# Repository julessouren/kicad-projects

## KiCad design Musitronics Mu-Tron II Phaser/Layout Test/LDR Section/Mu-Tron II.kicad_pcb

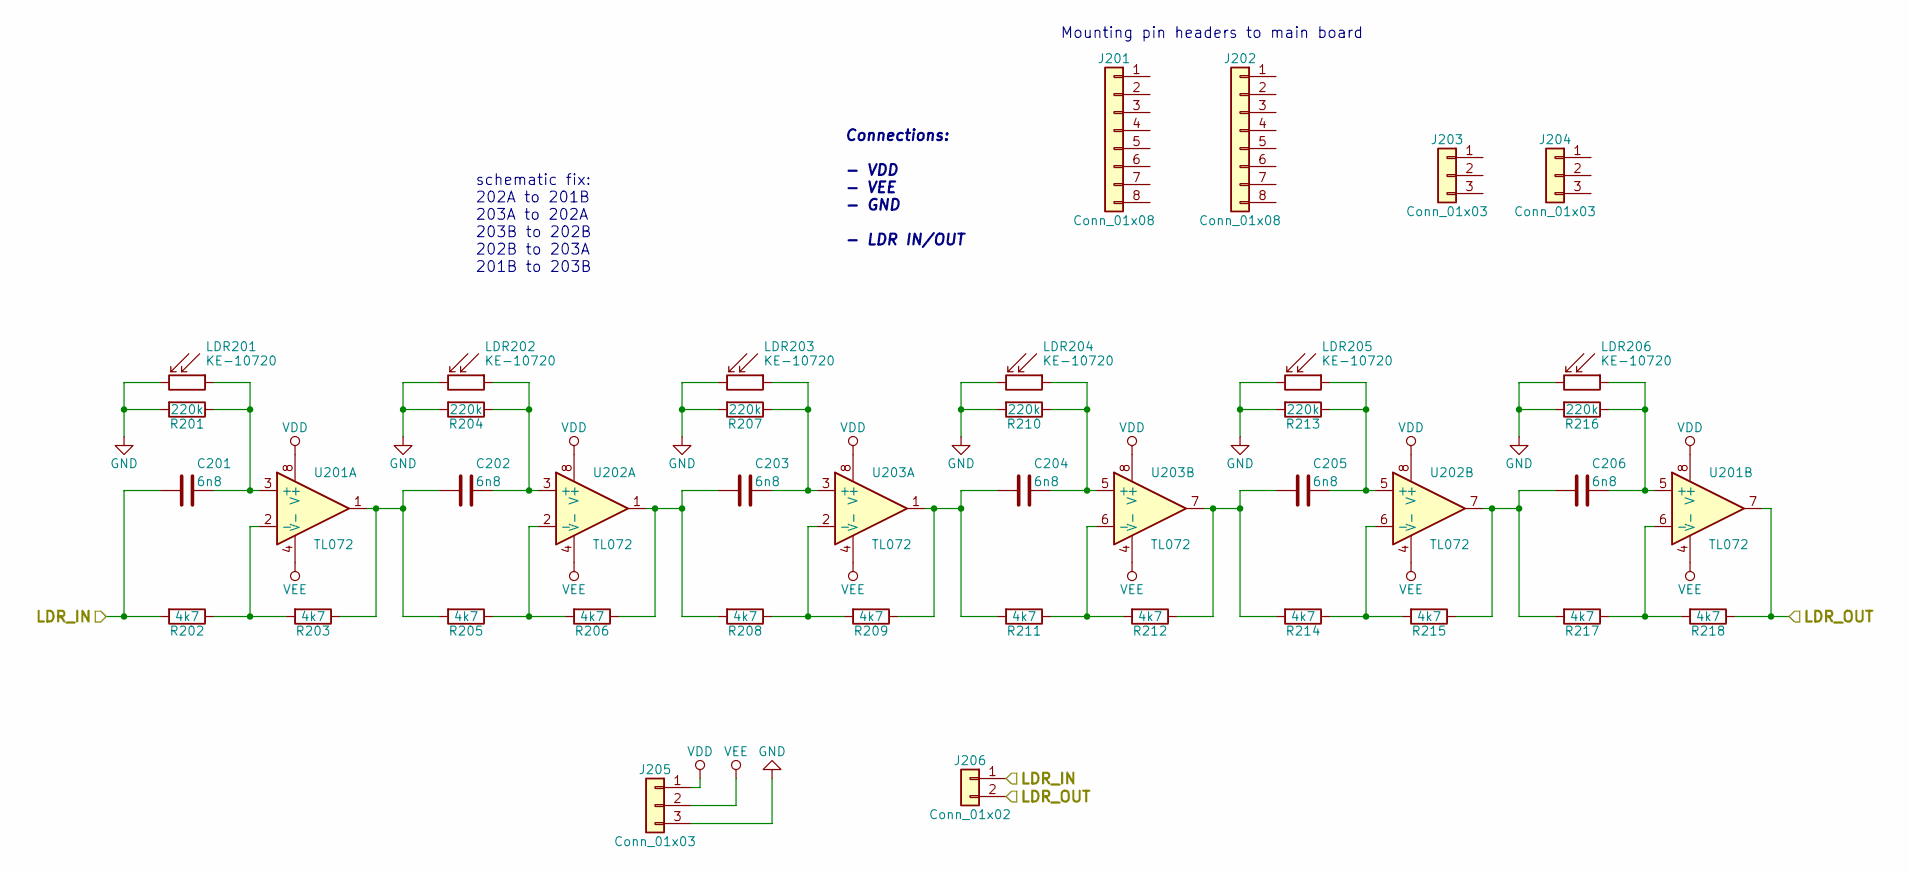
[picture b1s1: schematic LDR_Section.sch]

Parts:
C201, C202, C203, C204, C205, C206: 6n8; C_0603_1608M
J201, J202: Conn_01x08; PinHeader_1x08_P2.54mm_Vertical_Bottom
J203, J204, J205: Conn_01x03; PinHeader_1x03_P1.27mm_Vertical
J206: Conn_01x02; PinHeader_1x02_P1.27mm_Vertical
LDR201, LDR202, LDR203, LDR204, LDR205, LDR206: KE-10720; R_LDR_5.1x4.3mm_P3.4mm_Vertical
R201, R204, R207, R210, R213, R216: 220k; R_0603_1608M
R202, R203, R205, R206, R208, R209, R211, R212, R214, R215, R217, R218: 4k7; R_0603_1608M
U201, U202, U203: TL072; SOIC-8_3.9x4.9mm_P1.27mm

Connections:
/LDR_Section/LDR_IN: C201.2, J201.8, J206.1, R202.2
/LDR_Section/LDR_OUT: J202.8, J206.2, R218.1, U201.7
GND: J205.3, LDR201.2, LDR202.2, LDR203.2, LDR204.2, LDR205.2, LDR206.2, R201.2, R204.2, R207.2, R210.2, R213.2, R216.2; also elsewhere on the board
unnamed: C201.1, LDR201.1, R201.1, U201.3 (+)
unnamed: C202.1, LDR202.1, R204.1, U202.3 (+)
unnamed: C202.2, R203.1, R205.2, U201.1
unnamed: C203.1, LDR203.1, R207.1, U203.3 (+)
unnamed: C203.2, R206.1, R208.2, U202.1
unnamed: C204.1, LDR204.1, R210.1, U203.5 (+)
unnamed: C204.2, R209.1, R211.2, U203.1
unnamed: C205.1, LDR205.1, R213.1, U202.5 (+)
unnamed: C205.2, R212.1, R214.2, U203.7
unnamed: C206.1, LDR206.1, R216.1, U201.5 (+)
unnamed: C206.2, R215.1, R217.2, U202.7
unnamed: R202.1, R203.2, U201.2 (-)
unnamed: R205.1, R206.2, U202.2 (-)
unnamed: R208.1, R209.2, U203.2 (-)
unnamed: R211.1, R212.2, U203.6 (-)
unnamed: R214.1, R215.2, U202.6 (-)
unnamed: R217.1, R218.2, U201.6 (-)
VDD: J205.1, U201.8 (V+), U202.8 (V+), U203.8 (V+); also elsewhere on the board
VEE: J205.2, U201.4 (V-), U202.4 (V-), U203.4 (V-); also elsewhere on the board

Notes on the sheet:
Connections: - VDD - VEE - GND - LDR IN/OUT
Mounting pin headers to main board
schematic fix: 202A to 201B 203A to 202A 203B to 202B 202B to 203A 201B to 203B

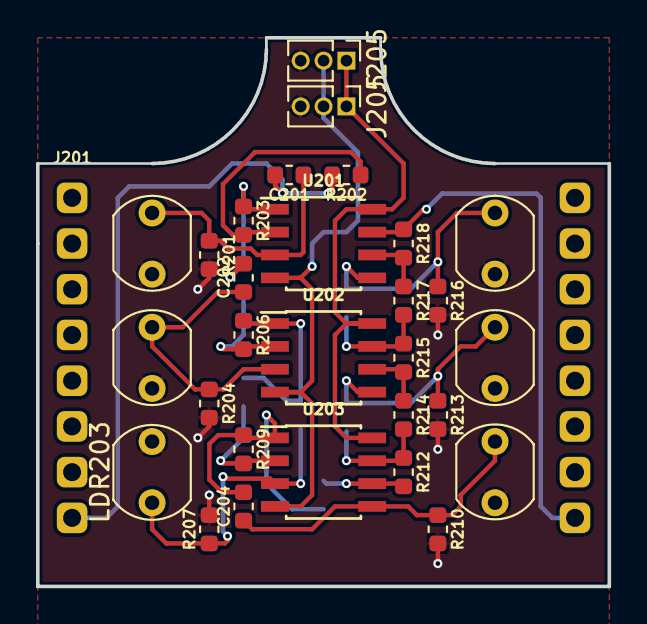
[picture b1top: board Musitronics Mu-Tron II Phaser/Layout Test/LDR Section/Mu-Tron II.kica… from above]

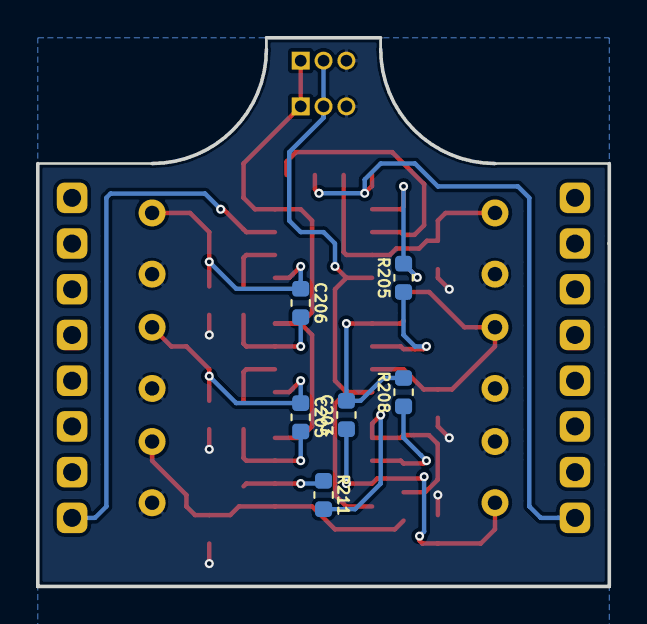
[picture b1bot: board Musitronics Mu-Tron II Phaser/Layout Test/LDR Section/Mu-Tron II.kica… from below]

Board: 2 copper layers, 31.8 x 30.5 mm, 37 parts (6 on the bottom side), 22 nets.

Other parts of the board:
J205#2: Conn_01x03; PinHeader_1x03_P1.27mm_Vertical

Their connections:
GND: J205#2.3; also elsewhere on the board
VDD: J205#2.1; also elsewhere on the board
VEE: J205#2.2; also elsewhere on the board

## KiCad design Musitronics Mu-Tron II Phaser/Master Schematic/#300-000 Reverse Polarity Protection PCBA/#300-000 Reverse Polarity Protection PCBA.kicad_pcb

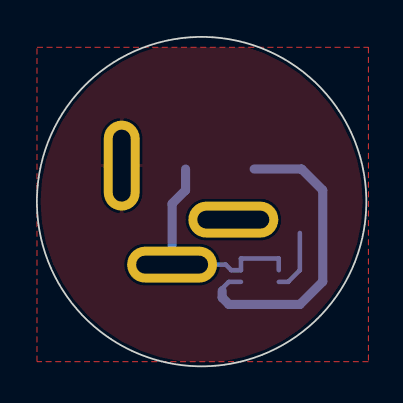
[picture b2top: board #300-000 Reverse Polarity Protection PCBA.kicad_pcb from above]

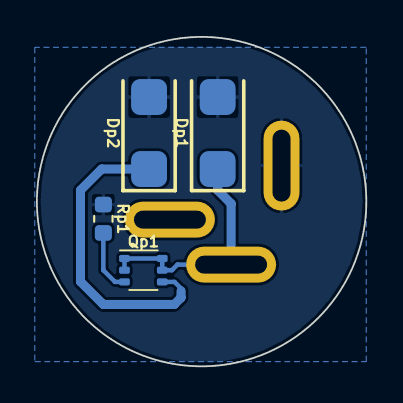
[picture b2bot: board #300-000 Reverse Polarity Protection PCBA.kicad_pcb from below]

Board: 2 copper layers, 18.3 x 18.3 mm, 5 parts (4 on the bottom side), 4 nets.

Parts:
Dp1, Dp2: 1SMA5924BT3G; ON_Semi_1SMA5924BT3G
Ja3: NEB_J_21_C; Lumberg_NEB_J_21_C
Qp1: MCH6341-TL-W; ON_Semi_MCH6341-TL-W
Rp1: 0R; R_0603_1608M

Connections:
GND: Dp1.1, Dp2.1, Ja3.1, Rp1.1
unnamed: Dp1.2, Ja3.2, Qp1.1, Qp1.2, Qp1.5, Qp1.6
unnamed: Qp1.3, Rp1.2
VCC: Dp2.2, Qp1.4

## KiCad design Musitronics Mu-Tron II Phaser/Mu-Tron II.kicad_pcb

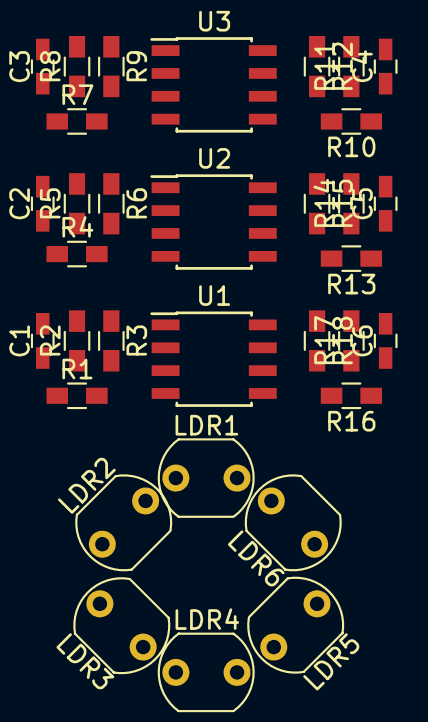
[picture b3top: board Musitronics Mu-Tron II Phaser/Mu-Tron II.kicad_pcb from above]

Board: 2 copper layers, 33 parts (0 on the bottom side), 20 nets, no tracks yet.

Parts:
C1, C2, C3, C4, C5, C6: 6n8; C_0603_HandSoldering
LDR1, LDR2, LDR3, LDR4, LDR5, LDR6: R_PHOTO; Resistor_LDR_5.1x4.3_RM3.4
R1, R4, R7, R10, R13, R16: 220k; R_0603_HandSoldering
R2, R3, R5, R6, R8, R9, R11, R12, R14, R15, R17, R18: 4k7; R_0603_HandSoldering
U1, U2, U3: NJM4558; SOIC-8_3.9x4.9mm_Pitch1.27mm

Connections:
GND: LDR1.2, LDR2.2, LDR3.2, LDR4.2, LDR5.2, LDR6.2, R1.2, R4.2, R7.2, R10.2, R13.2, R16.2, U1.4, U2.4, U3.4
unnamed: C1.1, LDR1.1, R1.1, U1.3
unnamed: C1.2, R2.2
unnamed: C2.1, LDR2.1, R4.1, U2.3
unnamed: C2.2, R3.1, R5.2, U1.1
unnamed: C3.1, LDR3.1, R7.1, U3.3
unnamed: C3.2, R6.1, R8.2, U2.1
unnamed: C4.1, LDR4.1, R10.1, U3.5
unnamed: C4.2, R9.1, R11.2, U3.1
unnamed: C5.1, LDR5.1, R13.1, U2.5
unnamed: C5.2, R12.1, R14.2, U3.7
unnamed: C6.1, LDR6.1, R16.1, U1.5
unnamed: C6.2, R15.1, R17.2, U2.7
unnamed: R2.1, R3.2, U1.2
unnamed: R5.1, R6.2, U2.2
unnamed: R8.1, R9.2, U3.2
unnamed: R11.1, R12.2, U3.6
unnamed: R14.1, R15.2, U2.6
unnamed: R17.1, R18.2, U1.6
unnamed: R18.1, U1.7

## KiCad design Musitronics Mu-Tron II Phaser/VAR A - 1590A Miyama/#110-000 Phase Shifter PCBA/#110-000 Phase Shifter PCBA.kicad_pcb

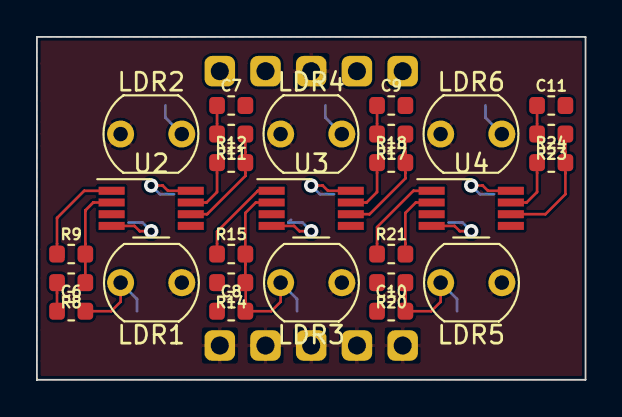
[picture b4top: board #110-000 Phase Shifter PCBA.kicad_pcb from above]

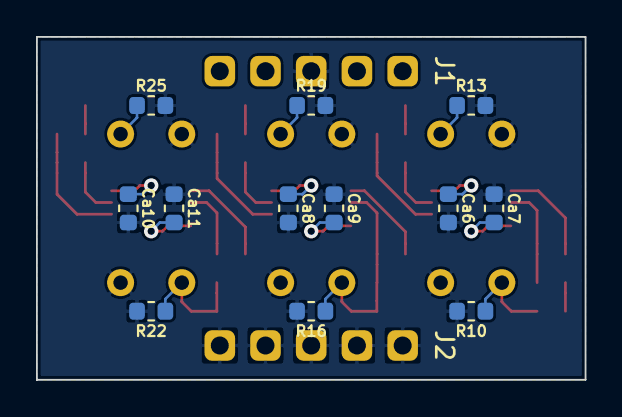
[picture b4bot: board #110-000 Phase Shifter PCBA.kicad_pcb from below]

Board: 2 copper layers, 30.5 x 19.0 mm, 41 parts (14 on the bottom side), 22 nets.

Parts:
C6, C7, C8, C9, C10, C11: 6n8; C_0603_1608M_h0.85
Ca6, Ca7, Ca8, Ca9, Ca10, Ca11: 100n; C_0603_1608M_h0.85
J1, J2: PinHeader_Straight_01x05_P2.54mm; PinHeader_1x05_P2.54mm_Vertical
LDR1, LDR2, LDR3, LDR4, LDR5, LDR6: KE-10720; Waitrony_KE-10720
R8, R9, R11, R12, R14, R15, R17, R18, R20, R21, R23, R24: 4k7; R_0603_1608M
R10, R13, R16, R19, R22, R25: 220k; R_0603_1608M
U2, U3, U4: 4558; Texas_Instruments_RC4558IDGKR

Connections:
GND: Ca6.2, Ca7.1, Ca8.2, Ca9.1, Ca10.2, Ca11.1, J1.3, J2.1, J2.2, J2.3, J2.4, J2.5, LDR1.1, LDR2.1, LDR3.1, LDR4.1, LDR5.1, LDR6.1, R10.2, R13.2, R16.2, R19.2, R22.2, R25.2
unnamed: C6.2, LDR1.2, R10.1, U2.3
unnamed: C7.1, R9.1, R11.2, U2.1
unnamed: C7.2, LDR2.2, R13.1, U2.5
unnamed: C8.1, R12.1, R14.2, U2.7
unnamed: C8.2, LDR3.2, R16.1, U3.3
unnamed: C9.1, R15.1, R17.2, U3.1
unnamed: C9.2, LDR4.2, R19.1, U3.5
unnamed: C10.1, R18.1, R20.2, U3.7
unnamed: C10.2, LDR5.2, R22.1, U4.3
unnamed: C11.1, R21.1, R23.2, U4.1
unnamed: C11.2, LDR6.2, R25.1, U4.5
unnamed: R8.1, R9.2, U2.2
unnamed: R11.1, R12.2, U2.6
unnamed: R14.1, R15.2, U3.2
unnamed: R17.1, R18.2, U3.6
unnamed: R20.1, R21.2, U4.2
unnamed: R23.1, R24.2, U4.6
PHASER_IN: C6.1, J1.1, R8.2
PHASER_OUT: J1.5, R24.1, U4.7
VCC: Ca6.1, Ca8.1, Ca10.1, J1.2, U2.8, U3.8, U4.8
VSS: Ca7.2, Ca9.2, Ca11.2, J1.4, U2.4, U3.4, U4.4

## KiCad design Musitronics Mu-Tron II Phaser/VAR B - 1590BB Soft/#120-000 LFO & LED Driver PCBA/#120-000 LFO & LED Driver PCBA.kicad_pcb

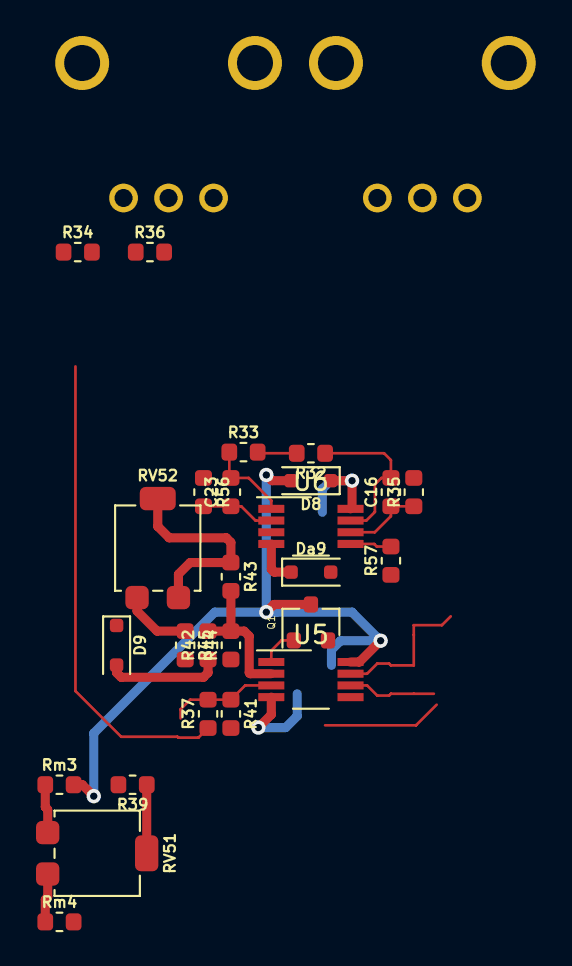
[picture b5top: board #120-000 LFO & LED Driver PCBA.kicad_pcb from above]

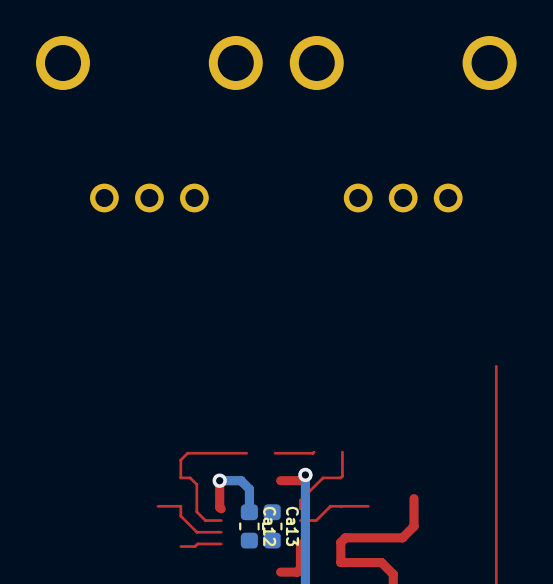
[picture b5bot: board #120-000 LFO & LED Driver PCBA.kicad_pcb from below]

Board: 2 copper layers, 30 parts (2 on the bottom side), 23 nets.

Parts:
C16: 470n; C_0603_1608M_h0.85
C23: 6n8; C_0603_1608M_h0.85
Ca12, Ca13: 100n; C_0603_1608M_h0.85
D8: 1N4148WS; ON_Semi_1N4148WS
D9: 4148; ON_Semi_1N4148WS
Da9: 1N4148WS; ON_Semi_1N4148WS
Q1: 3904; ON_Semi_SMMBT3904LT1G
R32, R39: 47k; R_0603_1608M
R33: 56k; R_0603_1608M
R34: 82R; R_0603_1608M
R35, R57: 27k; R_0603_1608M
R36: 560R; R_0603_1608M
R37: 82k; R_0603_1608M
R41: 3k3; R_0603_1608M
R42: 10k; R_0603_1608M
R43: 220k; R_0603_1608M
R44: 68k; R_0603_1608M
R45: 220R; R_0603_1608M
R56: 100k; R_0603_1608M
RV51: 10k; Bourns_3314G-1-104E
RV52: 1k; Bourns_3314G-1-104E
RV54: B10k; Alpha_Taiwan_RD901F-40
RV55: A25k; Alpha_Taiwan_RD901F-40
Rm3, Rm4: 0R; R_0603_1608M
U5, U6: 4558; Texas_Instruments_RC4558IDGKR

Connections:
GND: Ca12.2, Ca13.1, D9.2, R34.1, R36.1, R41.2, R44.1, R45.2, R56.1, R57.1, Rm4.2
unnamed: C16.1, R35.1, U6.6
unnamed: C16.2, R32.1, RV54.3, U6.7
unnamed: C23.1, R56.2, U6.2
unnamed: C23.2, R33.1, RV55.3, U6.1
unnamed: Ca12.1, D8.2, U6.8
unnamed: Ca13.2, Da9.2, U6.4
unnamed: D9.1, R42.1
unnamed: Q1.1, U5.1
unnamed: R32.2, R33.2, U6.3
unnamed: R34.2, RV55.1
unnamed: R35.2, RV55.2
unnamed: R36.2, RV54.1
unnamed: R37.1, RV54.2
unnamed: R37.2, R39.2, R41.1, U5.3
unnamed: R39.1, RV51.2
unnamed: R42.2, R43.2, R44.2, U5.2
unnamed: R45.1, RV52.3
unnamed: R57.2, U6.5
unnamed: RV51.1, Rm4.1
unnamed: RV51.3, Rm3.1
OC_LED_-: R43.1, RV52.1, RV52.2
VCC: D8.1, Q1.3, Rm3.2

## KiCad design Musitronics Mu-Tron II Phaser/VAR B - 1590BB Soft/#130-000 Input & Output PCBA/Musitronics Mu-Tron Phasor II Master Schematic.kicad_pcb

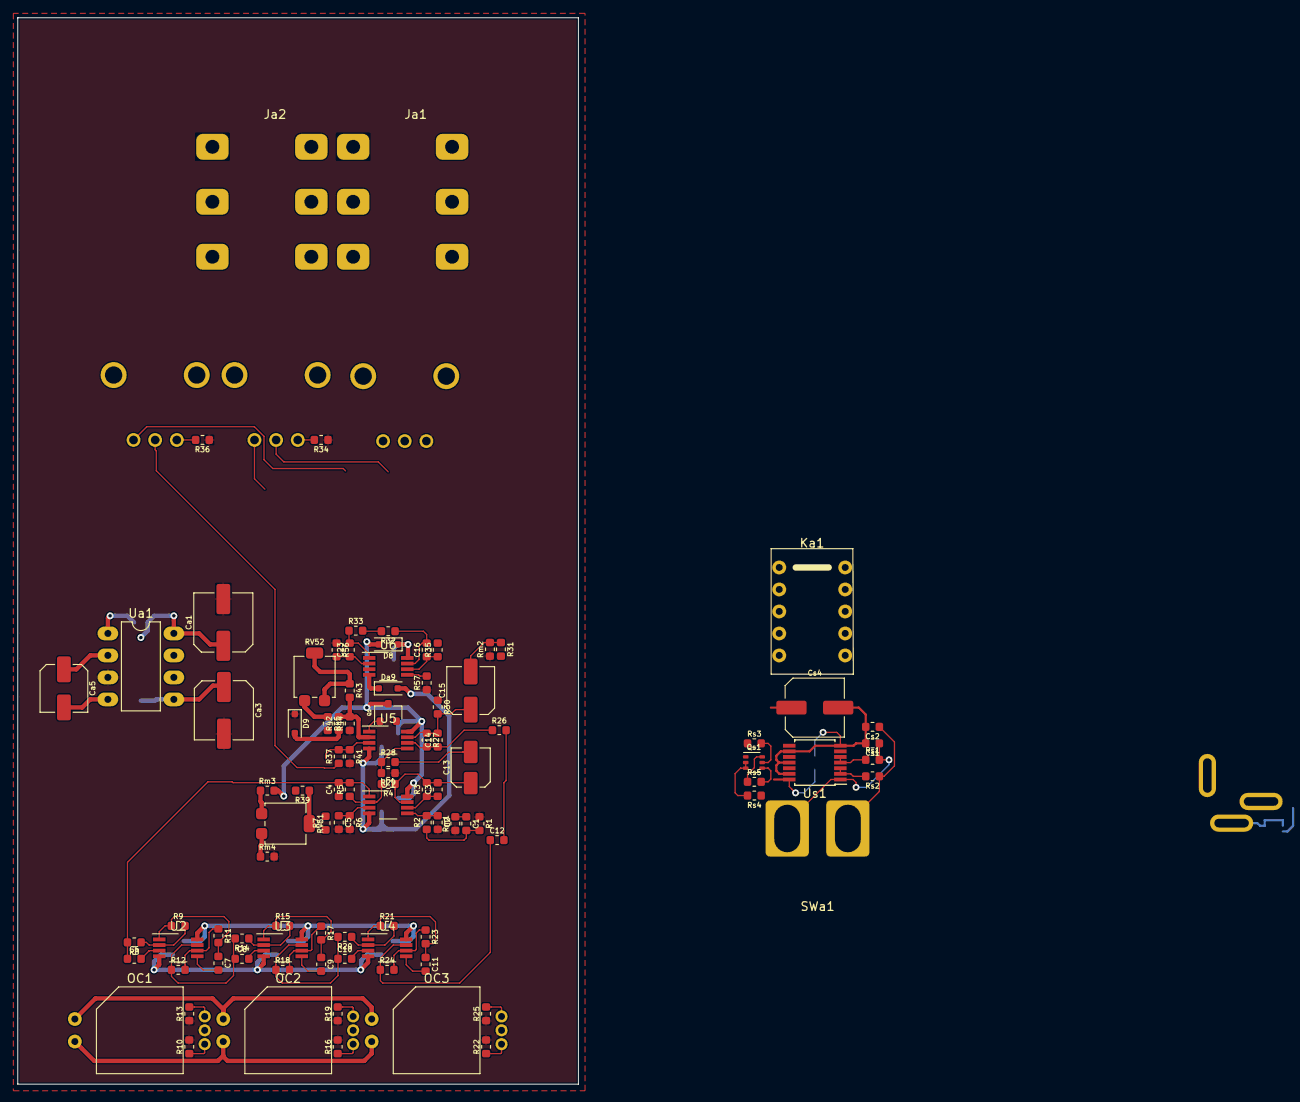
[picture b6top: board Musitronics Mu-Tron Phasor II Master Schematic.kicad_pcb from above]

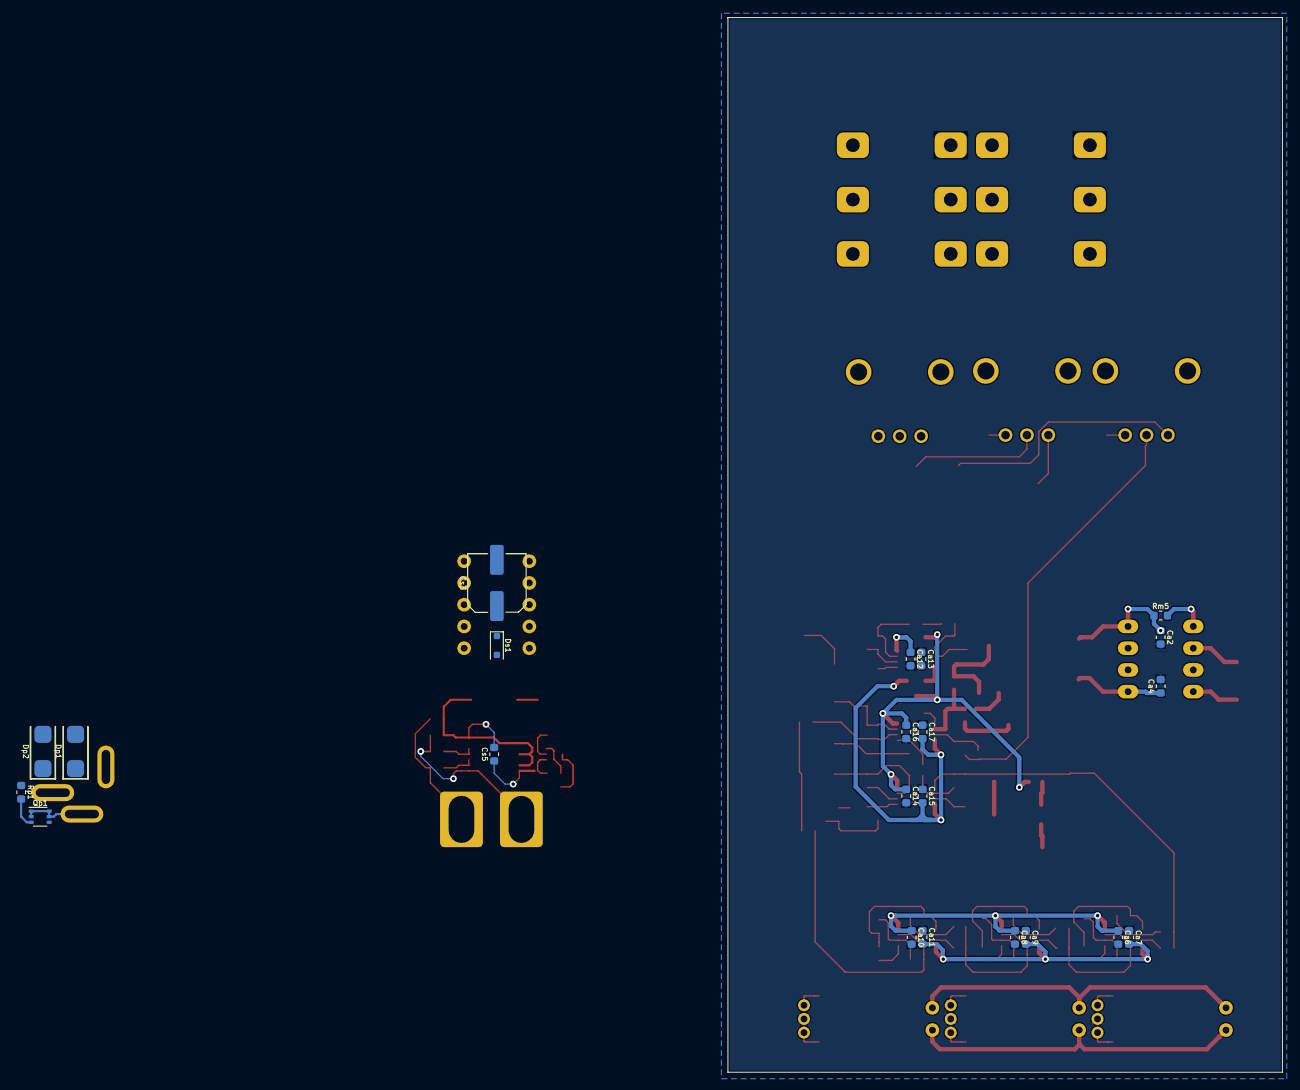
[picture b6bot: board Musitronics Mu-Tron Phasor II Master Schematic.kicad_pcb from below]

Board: 2 copper layers, 64.8 x 123.2 mm, 125 parts (25 on the bottom side), 75 nets.

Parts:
C1: 47n; C_0603_1608M_h0.85
C2: 33p; C_0603_1608M_h0.85
C3: 100n; C_0603_1608M_h0.85
C4: 1n; C_0603_1608M_h0.85
C5: 3n3; C_0603_1608M_h0.85
C6, C7, C8, C9, C10, C11, C23: 6n8; C_0603_1608M_h0.85
C12, C16: 470n; C_0603_1608M_h0.85
C13: 1u; Nichicon_UWT1H010MCL1GB
C14: 820p; C_0603_1608M_h0.85
C15: 10u; Nichicon_UWT1V100MCL1GB
Ca1, Ca3: 100u; Nichicon_UWT1E101MCL1GS
Ca2, Ca4, Ca6, Ca7, Ca8, Ca9, Ca10, Ca11, Ca12, Ca13, Ca14, Ca15, Ca16, Ca17: 100n; C_0603_1608M_h0.85
Ca5: 10u; Nichicon_UWT1V100MCL1GB
Cs1: 4n7; C_0603_1608M_h0.85
Cs2: 47n; C_0603_1608M_h0.85
Cs3, Cs4: 100u; Nichicon_UWT1E101MCL1GS
Cs5: 100n; C_0603_1608M_h0.85
D8: 1N4148WS; ON_Semi_1N4148WS
D9: 4148; ON_Semi_1N4148WS
Da9: 1N4148WS; ON_Semi_1N4148WS
Dp1, Dp2: 1SMA5924BT3G; ON_Semi_1SMA5924BT3G
Ds1: 1N4148WS; ON_Semi_1N4148WS
Ja1, Ja2: Amphenol_ACJS-MHOM
Ja3: NEB_J_21_C; Lumberg_NEB_J_21_C
Ka1: Kemet_EA2-5SNJ; Kemet_EA2-SNJ
OC1, OC2, OC3: Xvive_VTL5C3_2
Q1: 3904; ON_Semi_SMMBT3904LT1G
Qp1: MCH6341-TL-W; ON_Semi_MCH6341-TL-W
Qs1: MBT3946DW1T1G; ON_Semi_MBT3946DW1T1G
R1, R3: 390k; R_0603_1608M
R2: 3k9; R_0603_1608M
R4, R5, R6, R8, R9, R11, R12, R14, R15, R17, R18, R20, R21, R23, R24: 4k7; R_0603_1608M
R7, R27, R29: 8k2; R_0603_1608M
R10, R13, R16, R19, R22, R25, R43: 220k; R_0603_1608M
R26, R28, R42: 10k; R_0603_1608M
R30, R35, R57: 27k; R_0603_1608M
R31, R36: 560R; R_0603_1608M
R32, R39: 47k; R_0603_1608M
R33: 56k; R_0603_1608M
R34: 82R; R_0603_1608M
R37: 82k; R_0603_1608M
R41: 3k3; R_0603_1608M
R44: 68k; R_0603_1608M
R45: 220R; R_0603_1608M
R56: 100k; R_0603_1608M
RV51: 10k; Bourns_3314G-1-104E
RV52: 1k; Bourns_3314G-1-104E
RV53, RV54: B10k; Alpha_Taiwan_RD901F-40
RV55: A25k; Alpha_Taiwan_RD901F-40
Rm1, Rm2: 1M; R_0603_1608M
Rm3, Rm4, Rm5: 0R; R_0603_1608M
Rp1: 0R; R_0603_1608M
Rs1: 100k; R_0603_1608M
Rs2: 1M; R_0603_1608M
Rs3: 150k; R_0603_1608M
Rs4: 15k; R_0603_1608M
Rs5: 47R; R_0603_1608M
SWa1: SPST_NO; R13-85A1-05-HWH
U1, U2, U3, U4, U5, U6: 4558; Texas_Instruments_RC4558IDGKR
Ua1: MAX1044CPA
Us1: CD40106BPWR; Texas_Instruments_CD40106BPWR

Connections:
GND: C2.2, C5.2, Ca1.2, Ca2.2, Ca3.2, Ca4.2, Ca6.2, Ca7.1, Ca8.2, Ca9.1, Ca10.2, Ca11.1, Ca12.2, Ca13.1, Ca14.2, Ca15.1, Ca16.2, Ca17.1, Cs1.2, Cs2.2, Cs4.2, Cs5.2, D9.2, Dp1.1, Dp2.1, Ja1.S, Ja2.S, Ja3.1, Ka1.2, Ka1.10, OC1.4, OC2.4, OC3.4, Qs1.1, R1.1, R6.2, R10.2, R13.1, R16.2, R19.1, R22.2, R25.1, R29.1, R30.1, R34.1, R36.1, R41.2, R44.1, R45.2, R56.1, R57.1, RV53.1, Rm1.1, Rm2.1, Rm4.2, Rp1.1, Rs3.1, Rs4.1, Ua1.3, Us1.7, Us1.9, Us1.11, Us1.13
INPUT: Ja1.T, Ka1.4, Ka1.9
unnamed: C1.2, R1.2, R2.1
unnamed: C2.1, R2.2, U1.5
unnamed: C3.1, R3.1, U1.6
unnamed: C4.1, R4.2, R5.1, U1.2
unnamed: C5.1, R6.1, R7.2, U1.3
unnamed: C6.2, OC1.5, R10.1, U2.3
unnamed: C7.1, R9.1, R11.2, U2.1
unnamed: C7.2, OC1.3, R13.2, U2.5
unnamed: C8.1, R12.1, R14.2, U2.7
unnamed: C8.2, OC2.5, R16.1, U3.3
unnamed: C9.1, R15.1, R17.2, U3.1
unnamed: C9.2, OC2.3, R19.2, U3.5
unnamed: C10.1, R18.1, R20.2, U3.7
unnamed: C10.2, OC3.5, R22.1, U4.3
unnamed: C11.1, R21.1, R23.2, U4.1
unnamed: C11.2, OC3.3, R25.2, U4.5
unnamed: C12.2, R26.2, RV53.3
unnamed: C3.2, C13.1, R3.2, R4.1, U1.7
unnamed: C13.2, R28.2
unnamed: C14.1, R26.1, R27.2, U5.6
unnamed: C14.2, C15.1, R27.1, R30.2, U5.7
unnamed: C15.2, R31.1, Rm2.2
unnamed: C16.1, R35.1, U6.6
unnamed: C16.2, R32.1, RV54.3, U6.7
unnamed: C23.1, R56.2, U6.2
unnamed: C23.2, R33.1, RV55.3, U6.1
unnamed: Ca5.1, Ua1.2
unnamed: Ca5.2, Ua1.4
unnamed: Ca12.1, D8.2, U6.8
unnamed: Ca13.2, Da9.2, U6.4
unnamed: Cs1.1, Rs1.2, SWa1.1, Us1.1
unnamed: Cs2.1, Rs2.1, SWa1.2
unnamed: Cs3.1, Ds1.2, Qs1.4, Rs5.2
unnamed: Cs3.2, Ka1.1
unnamed: D9.1, R42.1
unnamed: Dp1.2, Ja3.2, Qp1.1, Qp1.2, Qp1.5, Qp1.6
unnamed: Ds1.1, Qs1.5, Rs3.2, Us1.6
unnamed: Q1.1, U5.1
unnamed: Qp1.3, Rp1.2
unnamed: Qs1.2, Qs1.3, Rs4.2
unnamed: Qs1.6, Rs5.1
unnamed: R7.1, RV53.2
unnamed: R8.1, R9.2, U2.2
unnamed: R11.1, R12.2, U2.6
unnamed: R14.1, R15.2, U3.2
unnamed: R17.1, R18.2, U3.6
unnamed: R20.1, R21.2, U4.2
unnamed: R23.1, R24.2, U4.6
unnamed: R28.1, R29.2, U5.5
unnamed: R32.2, R33.2, U6.3
unnamed: R34.2, RV55.1
unnamed: R35.2, RV55.2
unnamed: R36.2, RV54.1
unnamed: R37.1, RV54.2
unnamed: R37.2, R39.2, R41.1, U5.3
unnamed: R39.1, RV51.2
unnamed: R42.2, R43.2, R44.2, U5.2
unnamed: R45.1, RV52.3
unnamed: R57.2, U6.5
unnamed: RV51.1, Rm4.1
unnamed: RV51.3, Rm3.1
unnamed: Rm5.2, Ua1.1
unnamed: Rs1.1, Us1.4, Us1.5
unnamed: Rs2.2, Us1.2, Us1.3
OC_LED_+: OC1.2, OC2.2, OC3.2, Q1.2
OC_LED_-: OC1.1, OC2.1, OC3.1, R43.1, RV52.1, RV52.2
OUTPUT: Ja2.T, Ka1.8
PHASER_IN: C4.2, C6.1, R5.2, R8.2, U1.1
PHASER_OUT: C12.1, R24.1, U4.7
RETURN: Ka1.7, R31.2
SEND: C1.1, Ka1.3, Rm1.2
VCC: Ca1.1, Ca2.1, Ca6.1, Ca8.1, Ca10.1, Ca14.1, Ca16.1, Cs4.1, Cs5.1, D8.1, Dp2.2, Q1.3, Qp1.4, Rm3.2, Rm5.1, U1.8, U2.8, U3.8, U4.8, U5.8, Ua1.8, Us1.14
VSS: Ca3.1, Ca4.1, Ca7.2, Ca9.2, Ca11.2, Ca15.2, Ca17.2, Da9.1, U1.4, U2.4, U3.4, U4.4, U5.4, Ua1.5
